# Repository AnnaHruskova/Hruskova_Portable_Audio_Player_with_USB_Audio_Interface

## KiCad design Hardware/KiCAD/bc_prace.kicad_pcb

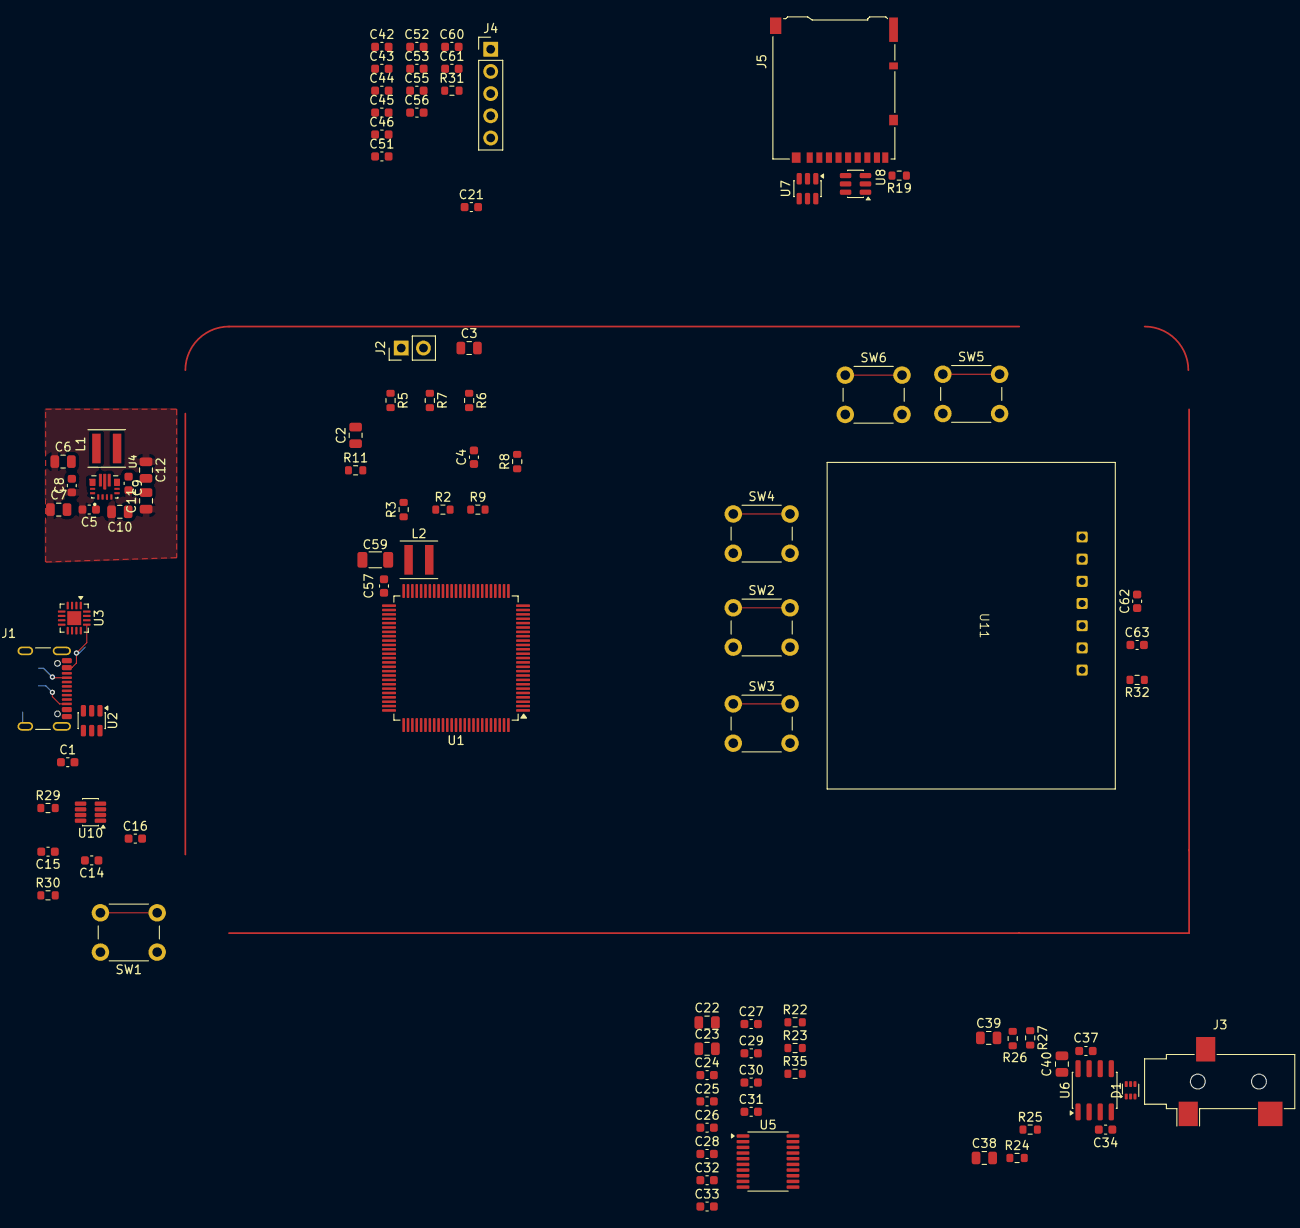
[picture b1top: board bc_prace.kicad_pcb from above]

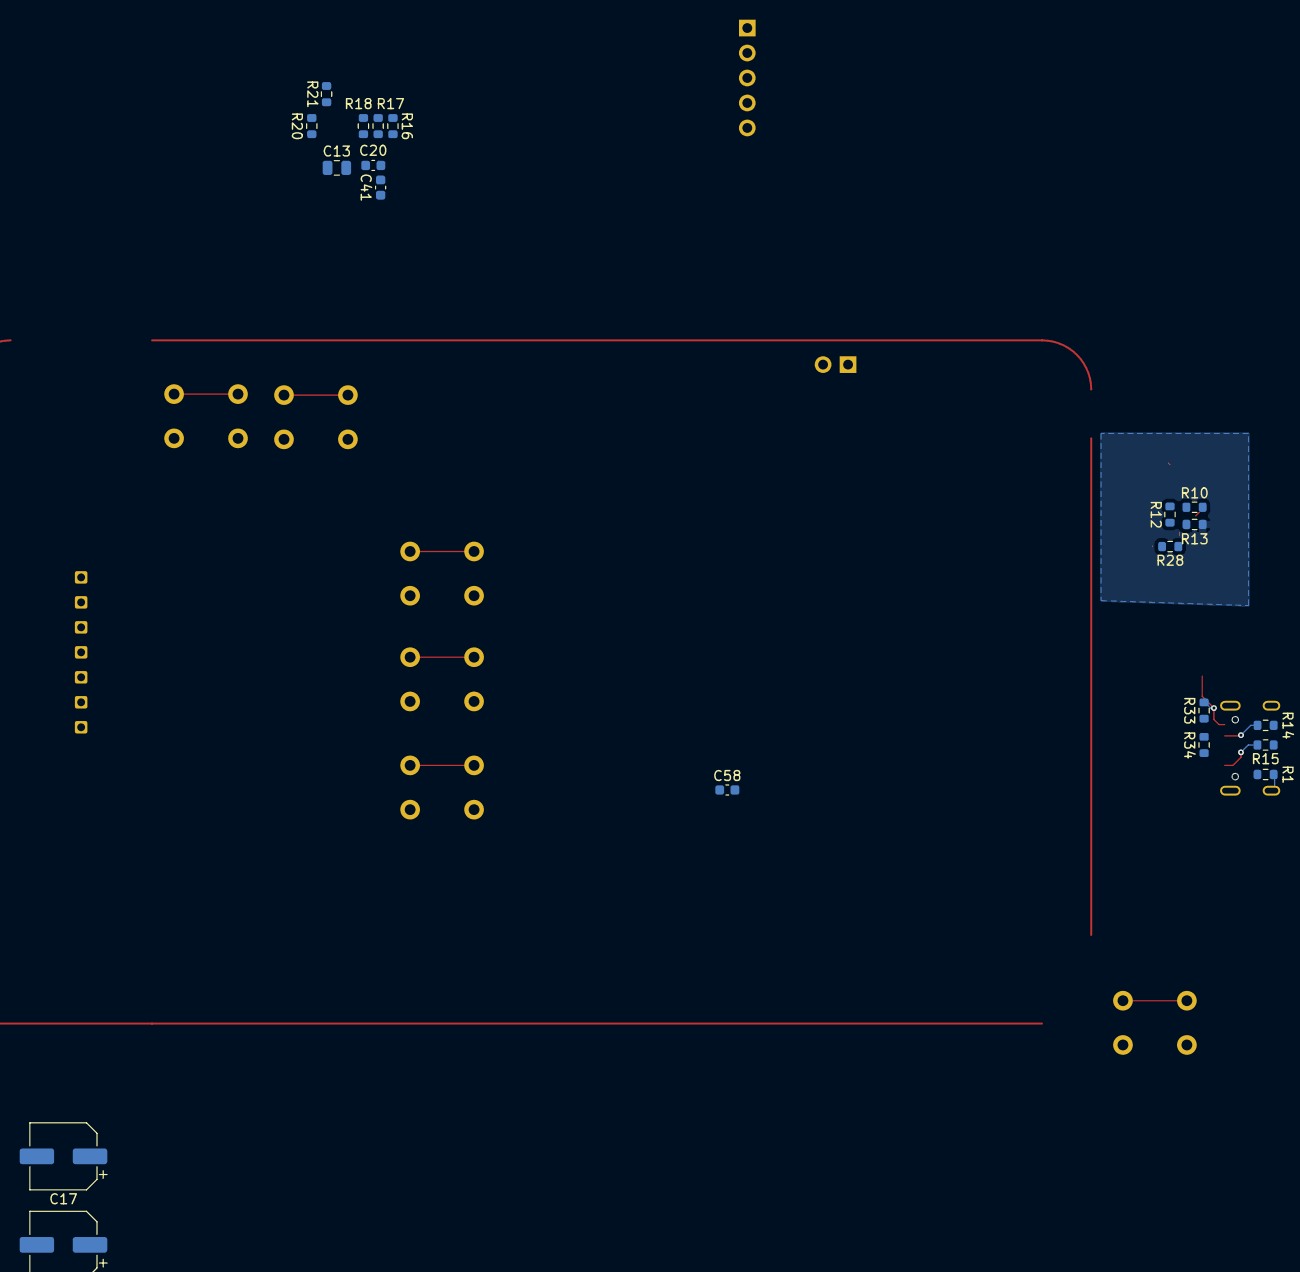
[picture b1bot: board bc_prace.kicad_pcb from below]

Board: 4 copper layers, 113 parts (20 on the bottom side), 77 nets.

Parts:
C1, C5, C14, C20, C41, C42, C43, C44, C45, C46, C51, C52, C53, C56, C60, C62: 100n; C_0603_1608Metric
C2, C3: 4.7u; C_0805_2012Metric
C4, C63: 4.7u; C_0603_1608Metric
C6, C7, C40: 10u; C_0805_2012Metric
C8, C9, C21, C27, C29, C31, C32: 10u; C_0603_1608Metric
C10, C11, C12, C13: 22u; C_0805_2012Metric
C15, C34, C55, C61: 1u; C_0603_1608Metric
C16: 330n; C_0603_1608Metric
C17, C18: 470u; CP_Elec_6.3x7.7
C22, C23, C38, C39: 2.2u; C_0805_2012Metric
C24, C25: 2.2n; C_0603_1608Metric
C26, C28, C30, C33, C37: 0.1u; C_0603_1608Metric
C57, C58: 2.2u; C_0603_1608Metric
C59: 10u; C_1206_3216Metric
D1: TPD2E1B06DRLR; SOT-563
J1: USB_C_Receptacle_USB2.0_16P; USB_C_Receptacle_GCT_USB4105-xx-A_16P_TopMnt_Horizontal
J2: BATTERY_RCY; PinHeader_1x02_P2.54mm_Vertical
J3: SJ-3523-SMT-TR; Jack_3.5mm_CUI_SJ-3523-SMT_Horizontal
J4: Conn_01x05; PinHeader_1x05_P2.54mm_Vertical
J5: DM3AT-SF-PEJM5; microSD_HC_Hirose_DM3AT-SF-PEJM5
L1: 1.5u; L_Coilcraft_XxL4020
L2: 2.2u; L_Coilcraft_XxL4020
R1: 0; R_0603_1608Metric
R2, R28, R30, R35: 100K; R_0603_1608Metric
R3, R7: 68K; R_0603_1608Metric
R5: 3,16K; R_0603_1608Metric
R6: 3,6K; R_0603_1608Metric
R8, R9, R16, R17, R18, R19, R20, R21: 47K; R_0603_1608Metric
R10, R11, R29, R31, R32: 10K; R_0603_1608Metric
R12: 470K; R_0603_1608Metric
R13: 150K; R_0603_1608Metric
R14: 5.1k; R_0603_1608Metric
R15: 5.1K; R_0603_1608Metric
R22, R23: 470; R_0603_1608Metric
R24, R25, R26, R27: 20K; R_0603_1608Metric
R33: 33K; R_0603_1608Metric
R34: 82K; R_0603_1608Metric
SW1: POWER; SW_PUSH_6mm
SW2: PLAY; SW_PUSH_6mm
SW3: NEXT; SW_PUSH_6mm
SW4: PREV; SW_PUSH_6mm
SW5: VOL_UP; SW_PUSH_6mm
SW6: VOLL_DOWN; SW_PUSH_6mm
U1: STM32U575VITxQ; LQFP-100_14x14mm_P0.5mm
U2: USBLC6-2SC6; SOT-23-6
U3: BQ24074RGT; VQFN-16-1EP_3x3mm_P0.5mm_EP1.6x1.6mm
U4: TPS63070RNMR; VREG_TPS63070RNMR
U5: PCM5102A; TSSOP-20_4.4x6.5mm_P0.65mm
U6: TPA6111A2D; SOIC-8_3.9x4.9mm_P1.27mm
U7, U8: USBLC6-4SC6; SOT-23-6
U10: LTC2954ITS8-1; TSOT-23-8
U11: Display; OLED_SPI_7pin_P2.54mm

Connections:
+3.3V: C9.2, C10.2, C11.2, C12.2, C13.2, C20.2, C21.2, C26.1, C27.1, C28.1, C29.1, C30.2, C31.2, C37.2, C40.2, C41.1, C42.2, C43.2, C44.2, C45.2, C46.2, C51.2, C52.2, C55.2, C56.2, C59.1, C60.2, C61.2, C62.1, C63.1, J4.5, J5.4 (VDD), R8.1, R9.1, R12.2, R16.1, R17.1, R18.1, R19.1, R20.1, R21.1, R29.1, R30.1, R32.1, U1.6 (VBAT), U1.11 (VDD), U1.20 (VREF+), U1.21 (VDDA), U1.27 (VDD), U1.47 (VDDSMPS), U1.51 (VDD), U1.73 (VDDUSB), U1.75 (VDD), U1.100 (VDD), U4.7_8 (VOUT), U5.1 (CPVDD), U5.8 (AVDD), U5.20 (DVDD), U6.8 (VDD), U7.5 (VBUS), U8.5 (VBUS), U11.2 (VCC)
/DAC/DAC_BCLK: U1.4 (PE5), U5.13 (BCK)
/DAC/DAC_DIN: U1.5 (PE6), U5.14 (DIN)
/DAC/DAC_LRCK: U1.3 (PE4), U5.15 (LRCK)
/DAC/DAC_OUT_L: C24.2, C38.2, R22.2
/DAC/DAC_OUT_R: C25.2, C39.2, R23.2
/DAC/DAC_XSMT: R35.2, U1.24 (PA2), U5.17 (XSMT)
/DAC/LDOO: C32.1, C33.1, U5.18 (LDOO)
/DAC/VNEG: C23.2, U5.5 (VNEG)
/Headphone Amp/AMP_SHDW: U1.33 (PB1), U6.5 (SHUTDOWN)
/MCU/BTN_NEXT: SW3.1, U1.64 (PC7)
/MCU/BTN_PLAY: SW2.1, U1.63 (PC6)
/MCU/BTN_PREV: SW4.1, U1.81 (PD0)
/MCU/BTN_VOL_DOWN: SW6.1, U1.84 (PD3)
/MCU/BTN_VOL_UP: SW5.1, U1.82 (PD1)
/MCU/CHG_DISABLE: R3.2, U1.52 (PB13), U3.4 (~CE)
/MCU/CHG_EN1: R2.2, U1.53 (PB14), U3.6 (EN1)
/MCU/CHG_PGOOD: R9.2, U1.54 (PB15), U3.7 (~PGOOD)
/MCU/CHG_STATUS: R8.2, U1.15 (PC0), U3.9 (~CHG)
/MCU/D_M: U1.70 (PA11), U2.6 (I/O1)
/MCU/D_P: U1.71 (PA12), U2.4 (I/O2)
/MCU/LTC_INT: R29.2, U1.45 (PB11), U10.5 (INT)
/MCU/LTC_KILL: R30.2, U1.44 (PB10), U10.8 (KILL)
/MCU/NRST: C53.2, J4.3, U1.14 (NRST)
/MCU/OLED_CLK: U1.89 (PB3), U11.3 (CLK)
/MCU/OLED_CS: R32.2, U1.92 (PB6), U11.7 (CS)
/MCU/OLED_DC: U1.93 (PB7), U11.6 (DC)
/MCU/OLED_MOSI: U1.91 (PB5), U11.4 (MOSI)
/MCU/OLED_RST: U1.95 (PB8), U11.5 (RES)
/MCU/SD_CLK: J5.5 (CLK), U1.80 (PC12), U8.6 (I/O4)
/MCU/SD_CMD: J5.3 (CMD), R18.2, U1.83 (PD2), U8.4 (I/O3)
/MCU/SD_D0: J5.7 (DAT0), R19.2, U1.65 (PC8), U8.3 (I/O2)
/MCU/SD_D1: J5.8 (DAT1), R20.2, U1.66 (PC9), U8.1 (I/O1)
/MCU/SD_D2: J5.1 (DAT2), R16.2, U1.78 (PC10), U7.3 (I/O2)
/MCU/SD_D3: J5.2 (DAT3/CD), R17.2, U1.79 (PC11), U7.1 (I/O1)
/MCU/SD_DET: J5.10 (DET_A), R21.2, U1.32 (PB0), U7.4 (I/O3)
/MCU/SWCLK: J4.2, U1.76 (PA14)
/MCU/SWDIO: J4.1, U1.72 (PA13)
/MCU/VBUS_DET: R33.2, R34.1, U1.68 (PA9)
/Power/PWR_EN: R28.1, U4.14 (EN), U10.6 (EN)
/Power/bat_p: C3.1, J2.1, U3.2 (BAT), U3.3 (BAT)
/Power/sys_power: C2.2, C6.2, C7.2, C8.2, C14.2, R10.2, R28.2, U3.10 (OUT), U3.11 (OUT), U4.12_13 (VIN), U10.1 (VIN)
GND: C1.1, C2.1, C3.2, C4.1, C5.2, C6.1, C7.1, C8.1, C9.1, C10.1, C11.1, C12.1, C13.1, C14.1, C15.2, C16.2, C20.1, C21.1, C23.1, C24.1, C25.1, C26.2, C27.2, C28.2, C29.2, C30.1, C31.1, C32.2, C33.2, C34.2, C37.1, C40.1, C41.2, C42.1, C43.1, C44.1, C45.1, C46.1, C51.1, C52.1, C53.1, C55.1, C56.1, C57.1, C58.1, C59.2, C60.1, C61.1, C62.2, C63.2, D1.1 (IOA1), D1.4 (IOB2), J1.A1 (GND), J1.A12 (GND), J1.B1 (GND), J1.B12 (GND), J2.2, J3.S, J4.4, J5.6 (VSS), J5.9 (DET_B), J5.SH (SHIELD), R1.2, R2.1, R3.1, R5.1, R6.1, R7.1, R11.1, R13.2, R14.2, R15.1, R31.2, R34.2, R35.1, SW1.1, SW2.2, SW3.2, SW4.2, SW5.2, SW6.2, U1.10 (VSS), U1.19 (VSSA), U1.26 (VSS), U1.48 (VSSSMPS), U1.50 (VSS), U1.74 (VSS), U1.99 (VSS), U2.2 (GND), U3.5 (EN2), U3.8 (VSS), U3.17 (VSS), U4.4 (GND), U4.10 (PGND), U4.15 (VSEL), U5.3 (CPGND), U5.9 (AGND), U5.10 (DEMP), U5.11 (FLT), U5.12 (SCK), U5.16 (FMT), U5.19 (DGND), U6.4 (GND), U7.2 (GND), U8.2 (GND), U10.4 (GND), U11.1 (GND)
unnamed: C38.1, R24.1
unnamed: C39.1, R26.1
unnamed: C57.2, C58.2, L2.2, U1.49 (VDD11), U1.98 (VDD11)
unnamed: C17.2, D1.5 (IOA2), J3.R
unnamed: C18.2, D1.2 (IOB1), J3.T
unnamed: J1.A5 (CC1), R14.1
unnamed: J1.B5 (CC2), R15.2
unnamed: J1.A6 (D+), J1.B6 (D+), U2.3 (I/O2)
unnamed: J1.A7 (D-), J1.B7 (D-), U2.1 (I/O1)
unnamed: J1.SH (SHIELD), R1.1
unnamed: R31.1, U1.94 (PH3)
unnamed: L2.1, U1.46 (VLXSMPS)
unnamed: C1.2, C4.2, J1.A4 (VBUS), J1.A9 (VBUS), J1.B4 (VBUS), J1.B9 (VBUS), R33.1, U2.5 (VBUS), U3.13 (IN)
unnamed: R6.2, U3.12 (ILIM)
unnamed: R5.2, U3.16 (ISET)
unnamed: R7.2, U3.14 (TMR)
unnamed: R11.2, U3.1 (TS)
unnamed: R12.1, R13.1, U4.5 (FB)
unnamed: L1.2, U4.11 (L1)
unnamed: L1.1, U4.9 (L2)
unnamed: R10.1, U4.1 (PS/SYNC)
unnamed: C5.1, U4.3 (VAUX)
unnamed: C22.1, U5.4 (CAPM)
unnamed: C22.2, U5.2 (CAPP)
unnamed: R22.1, U5.6 (OUTL)
unnamed: R23.1, U5.7 (OUTR)
unnamed: C34.1, U6.3 (BYPASS)
unnamed: R24.2, R25.1, U6.2 (IN1-)
unnamed: R26.2, R27.2, U6.6 (IN2-)
unnamed: C18.1, R25.2, U6.1 (VO1)
unnamed: C17.1, R27.1, U6.7 (VO2)
unnamed: C16.1, U10.3 (ONT)
unnamed: SW1.2, U10.2 (PB)
unnamed: C15.1, U10.7 (PDT)

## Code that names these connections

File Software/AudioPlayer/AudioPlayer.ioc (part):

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Mcu.Name=STM32U575VITxQ
Mcu.Package=LQFP100
Mcu.UserName=STM32U575VITxQ
PA11.Mode=Device_Only
PA11.Signal=USB_OTG_FS_DM
PA12.Mode=Device_Only
PA12.Signal=USB_OTG_FS_DP
PA13\ (JTMS/SWDIO).Mode=Serial_Wire
PA13\ (JTMS/SWDIO).Signal=DEBUG_JTMS-SWDIO
PA14\ (JTCK/SWCLK).Mode=Serial_Wire
PA14\ (JTCK/SWCLK).Signal=DEBUG_JTCK-SWCLK
PA2.GPIOParameters=GPIO_Label
PA2.GPIO_Label=DAC_XSMT
PA2.Signal=GPIO_Output
PA9.GPIOParameters=GPIO_Label
PA9.GPIO_Label=USB_VBUS_DET
PA9.Signal=GPIO_Input
PB0.GPIOParameters=GPIO_Label
PB0.GPIO_Label=SD_DET
PB0.Signal=GPIO_Input
PB1.GPIOParameters=PinState,GPIO_Label
PB1.GPIO_Label=AMP_SHDW
PB1.PinState=GPIO_PIN_SET
PB1.Signal=GPIO_Output
PB10.GPIOParameters=PinState,GPIO_PuPd,GPIO_Label,GPIO_ModeDefaultOutputPP
PB10.GPIO_Label=LTC_KILL
PB10.GPIO_ModeDefaultOutputPP=GPIO_MODE_OUTPUT_OD
PB10.GPIO_PuPd=GPIO_NOPULL
PB10.PinState=GPIO_PIN_SET
PB10.Signal=GPIO_Output
PB11.GPIOParameters=GPIO_Label,GPIO_ModeDefaultEXTI
PB11.GPIO_Label=LTC_INT
PB11.GPIO_ModeDefaultEXTI=GPIO_MODE_IT_FALLING
PB11.Signal=GPXTI11
PB13.GPIOParameters=GPIO_Label
PB13.GPIO_Label=CHG_DISABLE
PB13.Signal=GPIO_Output
PB14.GPIOParameters=GPIO_Label
PB14.GPIO_Label=CHG_EN1
PB14.Signal=GPIO_Output
PB15.GPIOParameters=GPIO_Label
PB15.GPIO_Label=CHG_PGOOD
PB15.Signal=GPIO_Input
PB3\ (JTDO/TRACESWO).Mode=TX_Only_Simplex_Unidirect_Master
PB3\ (JTDO/TRACESWO).Signal=SPI1_SCK
PB5.Mode=TX_Only_Simplex_Unidirect_Master
PB5.Signal=SPI1_MOSI
PB6.GPIOParameters=PinState,GPIO_Label
PB6.GPIO_Label=OLED_CS
PB6.PinState=GPIO_PIN_SET
PB6.Signal=GPIO_Output
PB7.GPIOParameters=GPIO_Label
PB7.GPIO_Label=OLED_DC
PB7.Signal=GPIO_Output
PB8.GPIOParameters=PinState,GPIO_Label
PB8.GPIO_Label=OLED_RST
PB8.PinState=GPIO_PIN_SET
PB8.Signal=GPIO_Output
PC0.GPIOParameters=GPIO_Label
PC0.GPIO_Label=CHG_STATUS
PC0.Signal=GPIO_Input
PC10.Mode=SD_4_bits_Wide_bus
PC10.Signal=SDMMC1_D2
PC11.Mode=SD_4_bits_Wide_bus
PC11.Signal=SDMMC1_D3
PC12.Mode=SD_4_bits_Wide_bus
PC12.Signal=SDMMC1_CK
PC6.GPIOParameters=GPIO_PuPd,GPIO_Label
PC6.GPIO_Label=BTN_PLAY
PC6.GPIO_PuPd=GPIO_PULLUP
PC6.Signal=GPIO_Input
PC7.GPIOParameters=GPIO_PuPd,GPIO_Label
PC7.GPIO_Label=BTN_NEXT
PC7.GPIO_PuPd=GPIO_PULLUP
PC7.Signal=GPIO_Input
PC8.Mode=SD_4_bits_Wide_bus
PC8.Signal=SDMMC1_D0
PC9.Mode=SD_4_bits_Wide_bus
PC9.Signal=SDMMC1_D1
PD0.GPIOParameters=GPIO_PuPd,GPIO_Label
PD0.GPIO_Label=BTN_PREV
PD0.GPIO_PuPd=GPIO_PULLUP
PD0.Signal=GPIO_Input
PD1.GPIOParameters=GPIO_PuPd,GPIO_Label
PD1.GPIO_Label=BTN_VOL_UP
PD1.GPIO_PuPd=GPIO_PULLUP
PD1.Signal=GPIO_Input
PD2.Mode=SD_4_bits_Wide_bus
PD2.Signal=SDMMC1_CMD
PD3.GPIOParameters=GPIO_PuPd,GPIO_Label
PD3.GPIO_Label=BTN_VOL_DOWN
PD3.GPIO_PuPd=GPIO_PULLUP
PD3.Signal=GPIO_Input
PE4.Mode=SAI_A_Master
PE4.Signal=SAI1_FS_A
PE5.Mode=SAI_A_Master
PE5.Signal=SAI1_SCK_A
PE6.Mode=SAI_A_Master
PE6.Signal=SAI1_SD_A
RCC.HSE_VALUE=16000000
RCC.SYSCLKFreq_VALUE=48000000
board=custom
